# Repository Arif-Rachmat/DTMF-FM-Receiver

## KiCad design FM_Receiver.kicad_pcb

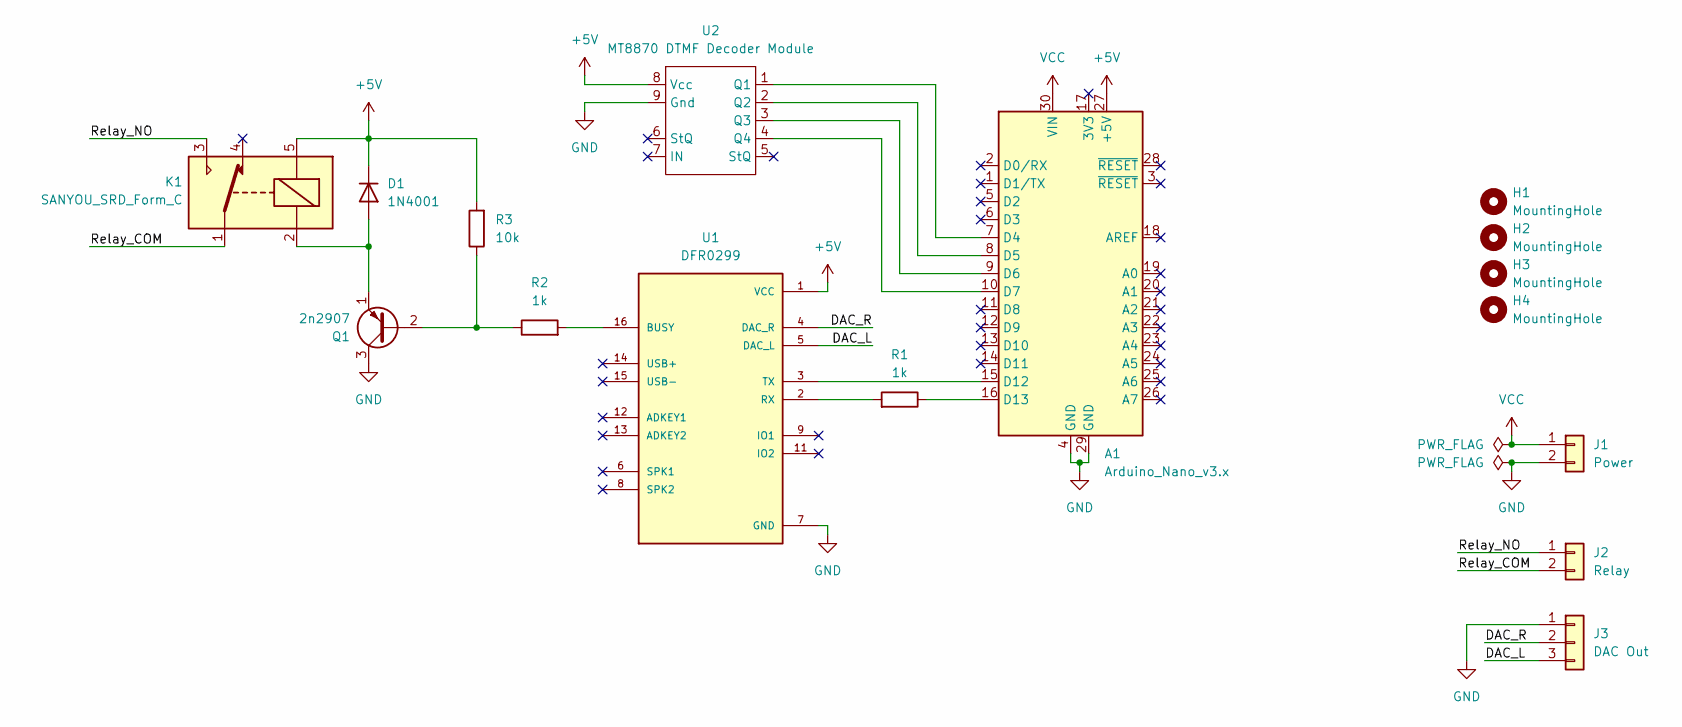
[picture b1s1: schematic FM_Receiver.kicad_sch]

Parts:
A1: Arduino_Nano_v3.x; Arduino_Nano
D1: 1N4001; D_DO-41_SOD81_P10.16mm_Horizontal
H1, H2, H3, H4: MountingHole; MountingHole_3.2mm_M3
J1: Power; Molex_KK-254_AE-6410-02A_1x02_P2.54mm_Vertical
J2: Relay; Molex_KK-254_AE-6410-02A_1x02_P2.54mm_Vertical
J3: DAC Out; Molex_KK-254_AE-6410-03A_1x03_P2.54mm_Vertical
K1: SANYOU_SRD_Form_C; Relay_SPDT_SANYOU_SRD_Series_Form_C
Q1: 2n2907; TO-92
R1, R2: 1k; R_Axial_DIN0207_L6.3mm_D2.5mm_P10.16mm_Horizontal
R3: 10k; R_Axial_DIN0207_L6.3mm_D2.5mm_P10.16mm_Horizontal
U1: DFR0299; MODULE_DFR0299
U2: MT8870 DTMF Decoder Module; MODULE_MT8870 DTMF

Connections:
+5V: A1.27 (+5V), D1.1 (K), K1.5, R3.2, U1.1 (VCC), U2.8 (Vcc)
/DAC_L: J3.3, U1.5 (DAC_L)
/DAC_R: J3.2, U1.4 (DAC_R)
/Relay_COM: J2.2, K1.1
/Relay_NO: J2.1, K1.3
GND: A1.4 (GND), A1.29 (GND), J1.2, J3.1, Q1.3 (C), U1.7 (GND), U1.10 (GND), U2.9 (Gnd)
unnamed: A1.7 (D4), U2.1 (Q1)
unnamed: A1.8 (D5), U2.2 (Q2)
unnamed: A1.9 (D6), U2.3 (Q3)
unnamed: A1.10 (D7), U2.4 (Q4)
unnamed: A1.15 (D12), U1.3 (TX)
unnamed: A1.16 (D13), R1.1
unnamed: D1.2 (A), K1.2, Q1.1 (E)
unnamed: Q1.2 (B), R2.1, R3.1
unnamed: R2.2, U1.16 (BUSY)
unnamed: R1.2, U1.2 (RX)
VCC: A1.30 (VIN), J1.1

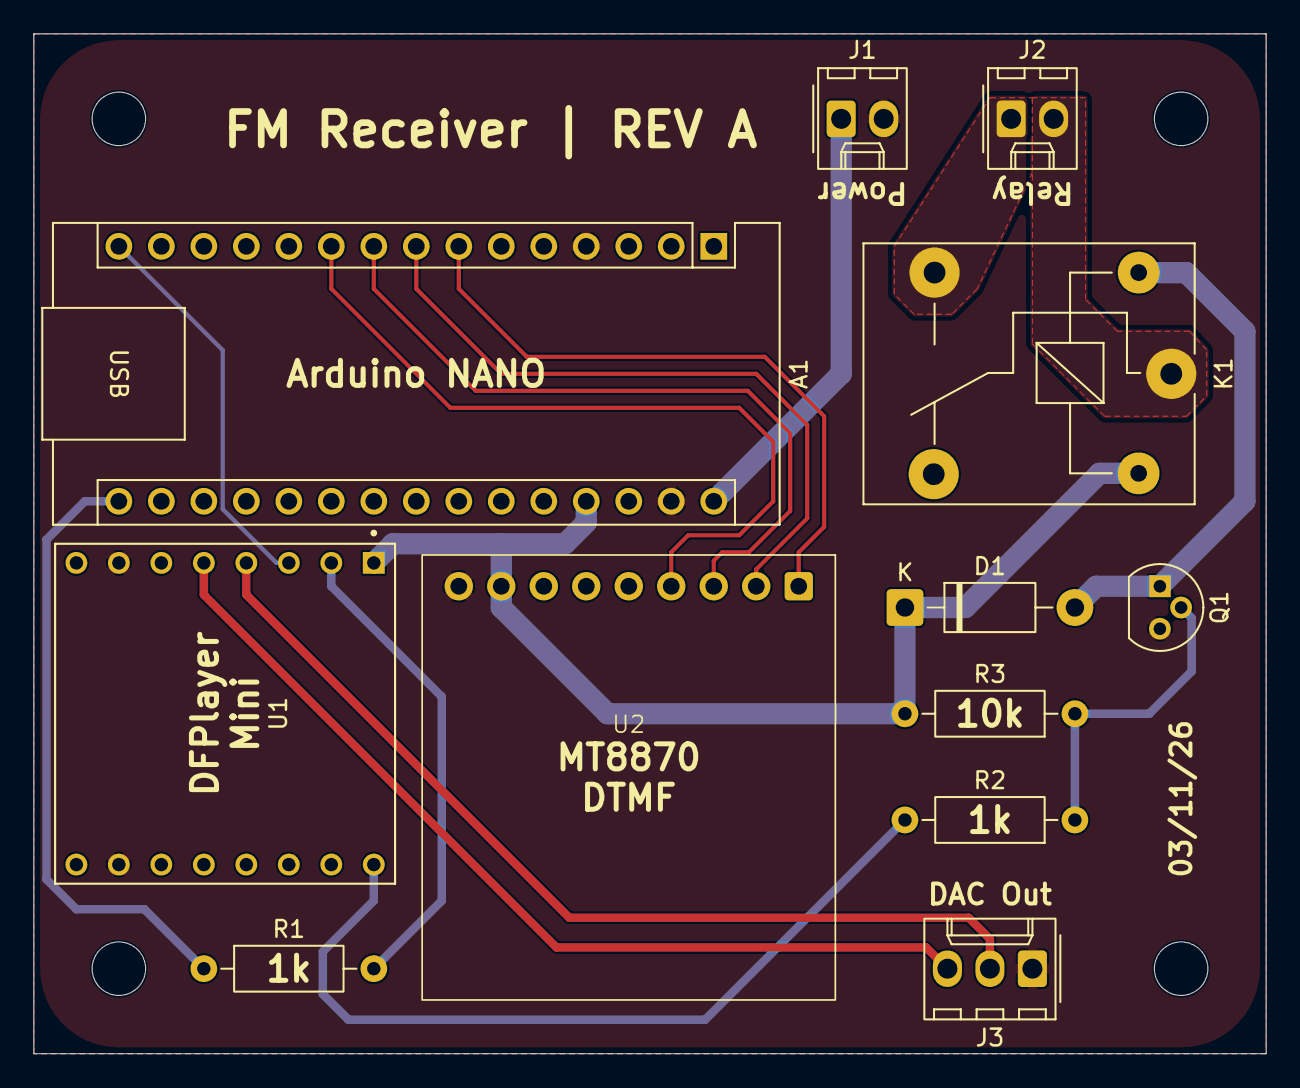
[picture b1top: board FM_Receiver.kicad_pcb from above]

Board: 2 copper layers, 73.7 x 61.0 mm, 16 parts (0 on the bottom side), 17 nets.
